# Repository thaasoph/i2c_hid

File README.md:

# i2c_hid
Board design and firmware for an ATTiny1616 as an I2C device with misc input options.

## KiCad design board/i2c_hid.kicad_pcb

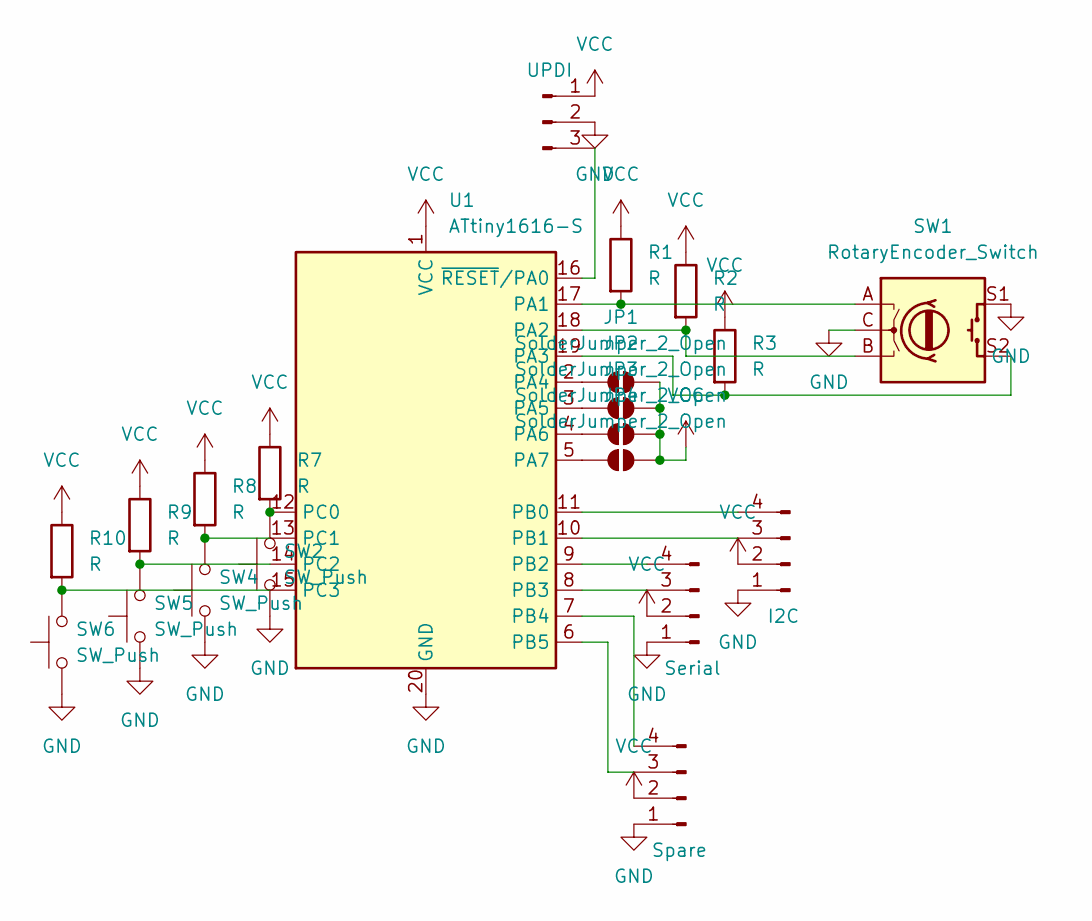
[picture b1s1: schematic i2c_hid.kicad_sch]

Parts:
J1: UPDI; PinHeader_1x03_P2.54mm_Vertical
J2: I2C; PinHeader_1x04_P2.54mm_Vertical
J3: Serial; PinHeader_1x04_P2.54mm_Vertical
J4: Spare; PinHeader_1x04_P2.54mm_Vertical
JP1, JP2, JP3, JP4: SolderJumper_2_Open; SolderJumper-2_P1.3mm_Open_Pad1.0x1.5mm
R1, R2, R3, R7, R8, R9, R10: R; R_Axial_DIN0207_L6.3mm_D2.5mm_P7.62mm_Horizontal
SW1: RotaryEncoder_Switch; RotaryEncoder_Alps_EC11E-Switch_Vertical_H20mm
SW2, SW4, SW5, SW6: SW_Push; SW_PUSH_6mm
U1: ATtiny1616-S; SOIC-20W_7.5x12.8mm_P1.27mm

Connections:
GND: J1.2, J2.1, J3.1, J4.1, SW1.C, SW1.S1, SW2.1, SW4.1, SW5.1, SW6.1, U1.20 (GND)
unnamed: J1.3, U1.16 (~RESET/PA0)
unnamed: J2.3, U1.10 (PB1)
unnamed: J2.4, U1.11 (PB0)
unnamed: J3.3, U1.8 (PB3)
unnamed: J3.4, U1.9 (PB2)
unnamed: J4.3, U1.6 (PB5)
unnamed: J4.4, U1.7 (PB4)
unnamed: JP1.1 (A), U1.2 (PA4)
unnamed: JP2.1 (A), U1.3 (PA5)
unnamed: JP3.1 (A), U1.4 (PA6)
unnamed: JP4.1 (A), U1.5 (PA7)
unnamed: R1.2, SW1.A, U1.17 (PA1)
unnamed: R2.2, SW1.B, U1.18 (PA2)
unnamed: R3.2, SW1.S2, U1.19 (PA3)
unnamed: R7.2, SW2.2, U1.12 (PC0)
unnamed: R8.2, SW4.2, U1.13 (PC1)
unnamed: R9.2, SW5.2, U1.14 (PC2)
unnamed: R10.2, SW6.2, U1.15 (PC3)
VCC: J1.1, J2.2, J3.2, J4.2, JP1.2 (B), JP2.2 (B), JP3.2 (B), JP4.2 (B), R1.1, R2.1, R3.1, R7.1, R8.1, R9.1, R10.1, U1.1 (VCC)

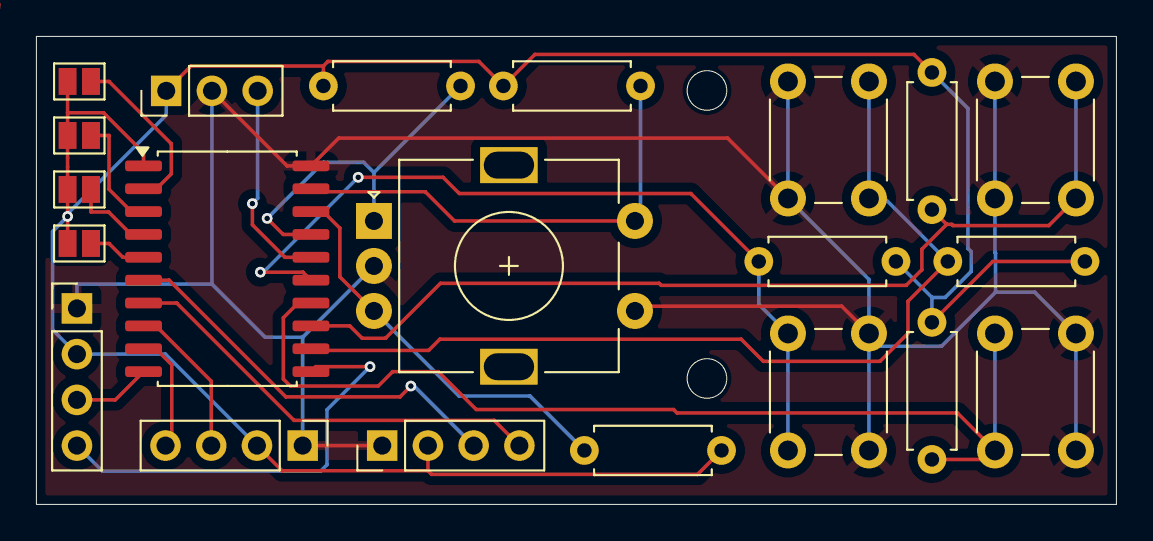
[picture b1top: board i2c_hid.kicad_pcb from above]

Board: 2 copper layers, 60.0 x 26.0 mm, 22 parts (0 on the bottom side), 20 nets.

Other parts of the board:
M2: MountingHole_2.2mm_M2

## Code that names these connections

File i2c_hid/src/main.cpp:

#include <EZButton.h>
#include <avr/io.h>
#include <avr/interrupt.h>
#include <util/delay.h>

// Attempt counter / watchdog for recovery
volatile uint8_t twiRecoveryAttempts = 0;
const uint8_t MAX_RECOVERY_ATTEMPTS = 3;

const uint8_t ADDRESS_BASE = 0x60;
uint8_t address = ADDRESS_BASE;

const uint8_t ROTARY_BTN_PIN = PIN_PA3;
const uint8_t ROTARY_A = PIN_PA1;
const uint8_t ROTARY_B = PIN_PA2;
const uint8_t BTN_1_PIN = PIN_PC0;
const uint8_t BTN_2_PIN = PIN_PC1;
const uint8_t BTN_3_PIN = PIN_PC2;
const uint8_t BTN_4_PIN = PIN_PC3;
const uint8_t fractionDebounce = 100;

volatile uint8_t busStatus = 0;

volatile int8_t rotationSteps = 0;
uint8_t buttonPress[5] = {0};
uint8_t buttonHold[5] = {0};

uint8_t responseBuffer[12] = {0};
volatile uint8_t bufferIndex = 0;

void ReadButtons(bool *states, int num)
{
  states[0] = !digitalRead(ROTARY_BTN_PIN);
  states[1] = !digitalRead(BTN_1_PIN);
  states[2] = !digitalRead(BTN_2_PIN);
  states[3] = !digitalRead(BTN_3_PIN);
  states[4] = !digitalRead(BTN_4_PIN);
}

void btnPress(int index)
{
  buttonPress[index]++;
}

void btnHold(int index)
{
  buttonHold[index]++;
}

// HoldThreshold: 500ms
// HoldInterval: 300ms
// DebounceTime: 15ms
EZButton _ezb(5, ReadButtons, 500, 300, 15);

void handleEncoder()
{
  static uint8_t lastState = 0;
  static long lastChange = 0;

  if (millis() - lastChange > fractionDebounce)
  {
    if (rotationSteps > -4 && rotationSteps < 4)
    {
      rotationSteps = 0;
    }
  }

  uint8_t state = (digitalRead(ROTARY_A) << 1) | digitalRead(ROTARY_B);

  // Transition table (Gray code)
  if ((lastState == 0b00 && state == 0b01) ||
      (lastState == 0b01 && state == 0b11) ||
      (lastState == 0b11 && state == 0b10) ||
      (lastState == 0b10 && state == 0b00))
  {
    rotationSteps++;
  }
  else if ((lastState == 0b00 && state == 0b10) ||
           (lastState == 0b10 && state == 0b11) ||
           (lastState == 0b11 && state == 0b01) ||
           (lastState == 0b01 && state == 0b00))
  {
    rotationSteps--;
  }

  lastState = state;
  lastChange = millis();
}

int8_t getAndResetRotationSteps()
{
  static long fractionSet;
  int8_t val;
  noInterrupts();
  val = rotationSteps / 4;
  if (val != 0)
  {
    rotationSteps = rotationSteps % 4;
    if (rotationSteps != 0)
    {
      fractionSet = millis();
    }
  }
  interrupts();
  return val;
}

void createResponseBuffer()
{
  uint8_t idx = 0;
  responseBuffer[idx++] = busStatus;
  responseBuffer[idx++] = getAndResetRotationSteps();
  memcpy(&responseBuffer[idx], &buttonPress, sizeof(buttonPress));
  memset(buttonPress, 0, sizeof(buttonPress));
  idx += sizeof(buttonPress);

  memcpy(&responseBuffer[idx], &buttonHold, sizeof(buttonHold));
  memset(buttonHold, 0, sizeof(buttonHold));
  idx += sizeof(buttonHold);
}

void recoverBus()
{
  // Disable interrupts around re-init
  uint8_t oldSREG = SREG;
  cli();
  TWI0.SCTRLA &= ~TWI_ENABLE_bm; // Disable TWI

  _delay_us(5);
  TWI0.SCTRLA |= TWI_ENABLE_bm; // Re-enable
  bufferIndex = 0;
  // Re-enable global interrupts
  SREG = oldSREG;

   // Track recovery attempts (optional): if too many, allow watchdog to reset
  if (++twiRecoveryAttempts >= MAX_RECOVERY_ATTEMPTS) {
    // let watchdog reset (or call a software reset)
    // wdt_enable(WDTO_1S); while(1);
  }
}

// === TWI0 Interrupt ===
ISR(TWI0_TWIS_vect)
{
  uint8_t status = TWI0.SSTATUS;

  // ---------- Bus error handling ----------
  if (status & (TWI_BUSERR_bm | TWI_ARBLOST_bm | TWI_COLL_bm))
  {
    busStatus |= status;
    TWI0.SSTATUS = TWI_BUSERR_bm | TWI_ARBLOST_bm | TWI_COLL_bm;
    recoverBus();
    return;
  }

  // ---------- Address match ----------
  if (status & TWI_APIF_bm)
  {
    bufferIndex = 0;
    TWI0.SSTATUS = TWI_APIF_bm; // clear flag
    return;
  }

  // ---------- Data transfer ----------
  if (status & TWI_DIF_bm)
  { // Data interrupt
    if (status & TWI_DIR_bm)
    { // Master reads

      if (bufferIndex == 0)
      {
        createResponseBuffer();
      }
      if (bufferIndex < sizeof(responseBuffer))
      {
        TWI0.SDATA = responseBuffer[bufferIndex++];
      }
      else
      {
        TWI0.SDATA = 0xFF; // End of buffer, send 0xFF
      }
    }
    else
    {                                     // Master writes
      volatile uint8_t data = TWI0.SDATA; // Read byte (ignore for now)
    }
    return;
  }

  // ---------- Stop condition ----------
  if (status & TWI_APIF_bm)
  {

    TWI0.SCTRLB = TWI_SCMD_COMPTRANS_gc;
    bufferIndex = 0;
    return;
  }
}

void initRotaryEncoder()
{
  pinMode(ROTARY_A, INPUT_PULLUP);
  pinMode(ROTARY_B, INPUT_PULLUP);

  attachInterrupt(digitalPinToInterrupt(ROTARY_A), handleEncoder, CHANGE);
  attachInterrupt(digitalPinToInterrupt(ROTARY_B), handleEncoder, CHANGE);
}

void initButtons()
{
  pinMode(ROTARY_BTN_PIN, INPUT_PULLUP);
  pinMode(BTN_1_PIN, INPUT_PULLUP);
  pinMode(BTN_2_PIN, INPUT_PULLUP);
  pinMode(BTN_3_PIN, INPUT_PULLUP);
  pinMode(BTN_4_PIN, INPUT_PULLUP);
  _ezb.Subscribe(0, btnHold, HOLD);
  _ezb.Subscribe(0, btnPress, RELEASED);
  _ezb.Subscribe(1, btnHold, HOLD);
  _ezb.Subscribe(1, btnPress, RELEASED);
  _ezb.Subscribe(2, btnHold, HOLD);
  _ezb.Subscribe(2, btnPress, RELEASED);
  _ezb.Subscribe(3, btnHold, HOLD);
  _ezb.Subscribe(3, btnPress, RELEASED);
  _ezb.Subscribe(4, btnHold, HOLD);
  _ezb.Subscribe(4, btnPress, RELEASED);
}

void initI2C()
{
  pinMode(PIN_PA6, INPUT_PULLUP);
  pinMode(PIN_PA7, INPUT_PULLUP);
  address |= !digitalRead(PIN_PA6);
  address |= !digitalRead(PIN_PA7) << 1;
  TWI0.SADDR = address << 1;                 // 7-bit address, LSB ignored
  TWI0.SCTRLA = TWI_ENABLE_bm | TWI_APIEN_bm // Address or Stop Interrupt Enable
                | TWI_DIEN_bm                // Data Interrupt Enable
                | TWI_PIEN_bm                // Stop Interrupt Enable
                | TWI_SMEN_bm;               // Smart Mode Enable
  TWI0.SCTRLB = 0;                           // Clear CTRLB
  TWI0.SSTATUS = TWI_BUSERR_bm;              // Clear bus error flag

  bufferIndex = 0;

  sei(); // Enable global interrupts
}

void setup()
{
  Serial0.begin(57600);
  initI2C();
  initRotaryEncoder();
  initButtons();
}

void loop()
{
  _ezb.Loop();
  // Serial0.printf("%d %d %d %d %d %d", rotationSteps, buttonPress[0], buttonPress[1], buttonPress[2], buttonPress[3], buttonPress[4]);
  // Serial0.println();
}

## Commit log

2025-08-24 Added board design
2025-08-24 Added project structure and crude implementation of solder bridge address
2025-08-24 Arrays initialized
2025-08-25 Added basic rotary encoder and button setup
2025-08-25 Removed IRAM_ATTR
2025-08-28 Added button library
2025-09-01 Added debugging statements for rotary encoder
2025-09-01 Reduced baud rate
2025-09-01 handled fractions and fixed serial out
2025-09-02 Ditched wire library
2025-09-02 added print statements
2025-09-02 added fixes
2025-09-03 Working bare metal sketch
